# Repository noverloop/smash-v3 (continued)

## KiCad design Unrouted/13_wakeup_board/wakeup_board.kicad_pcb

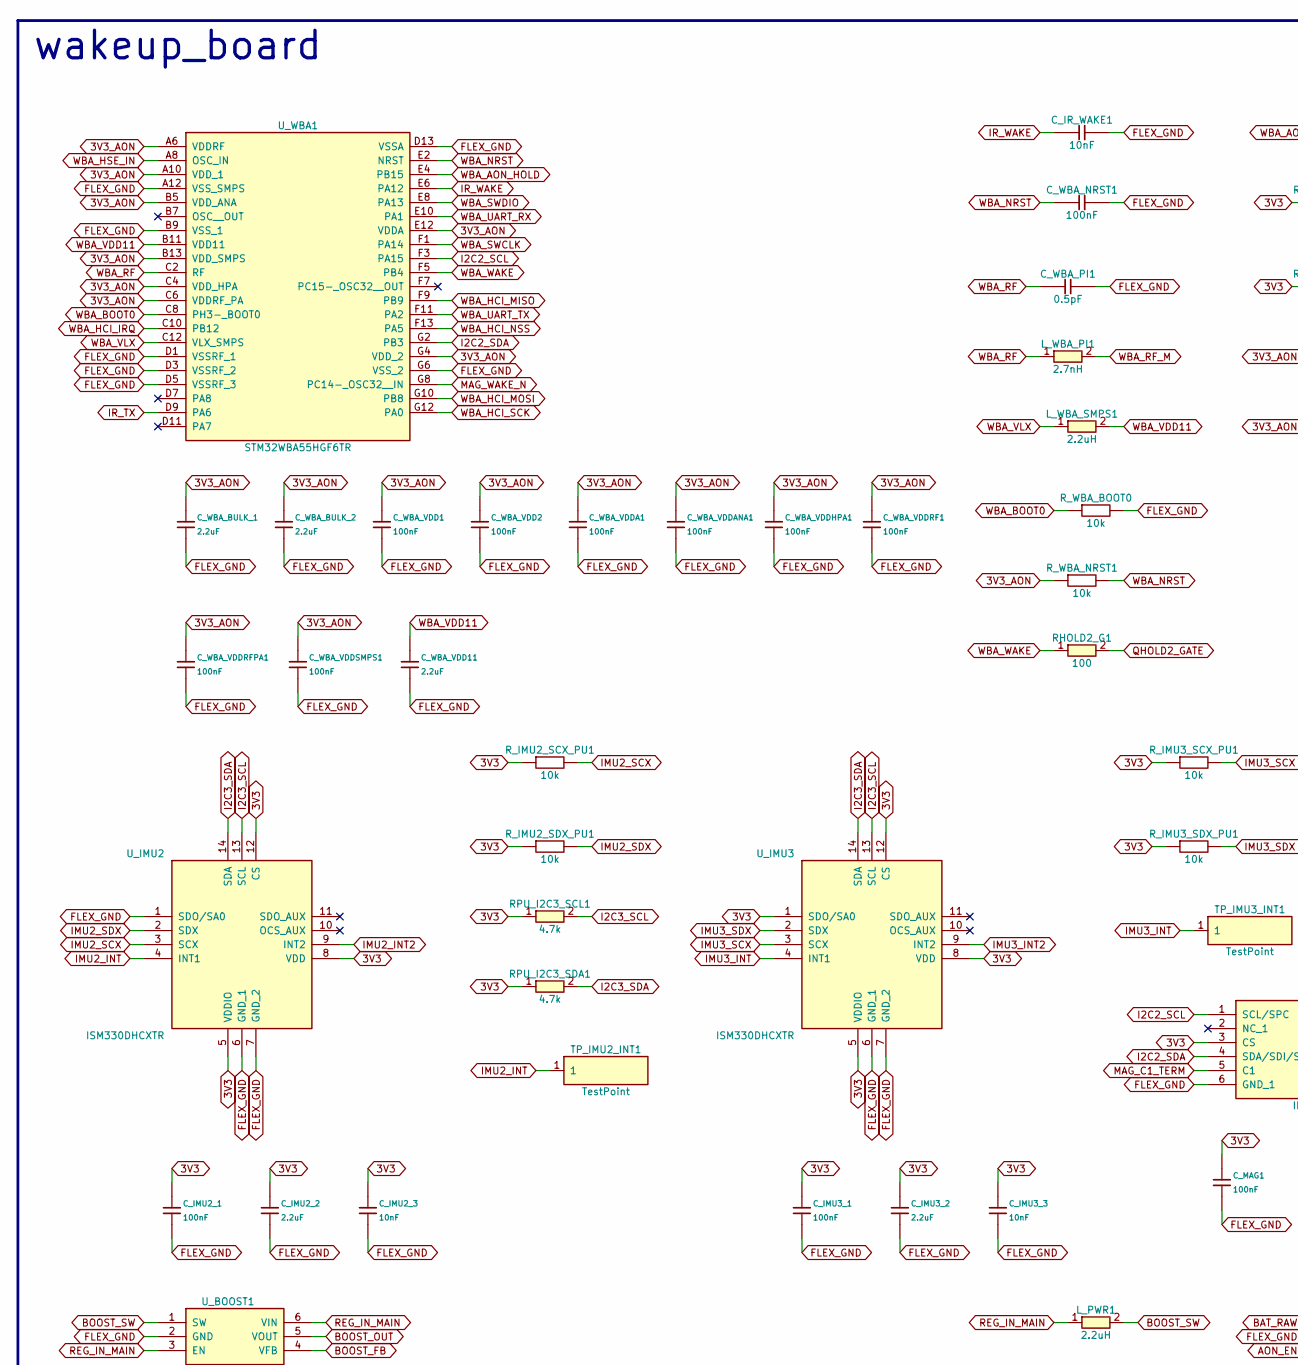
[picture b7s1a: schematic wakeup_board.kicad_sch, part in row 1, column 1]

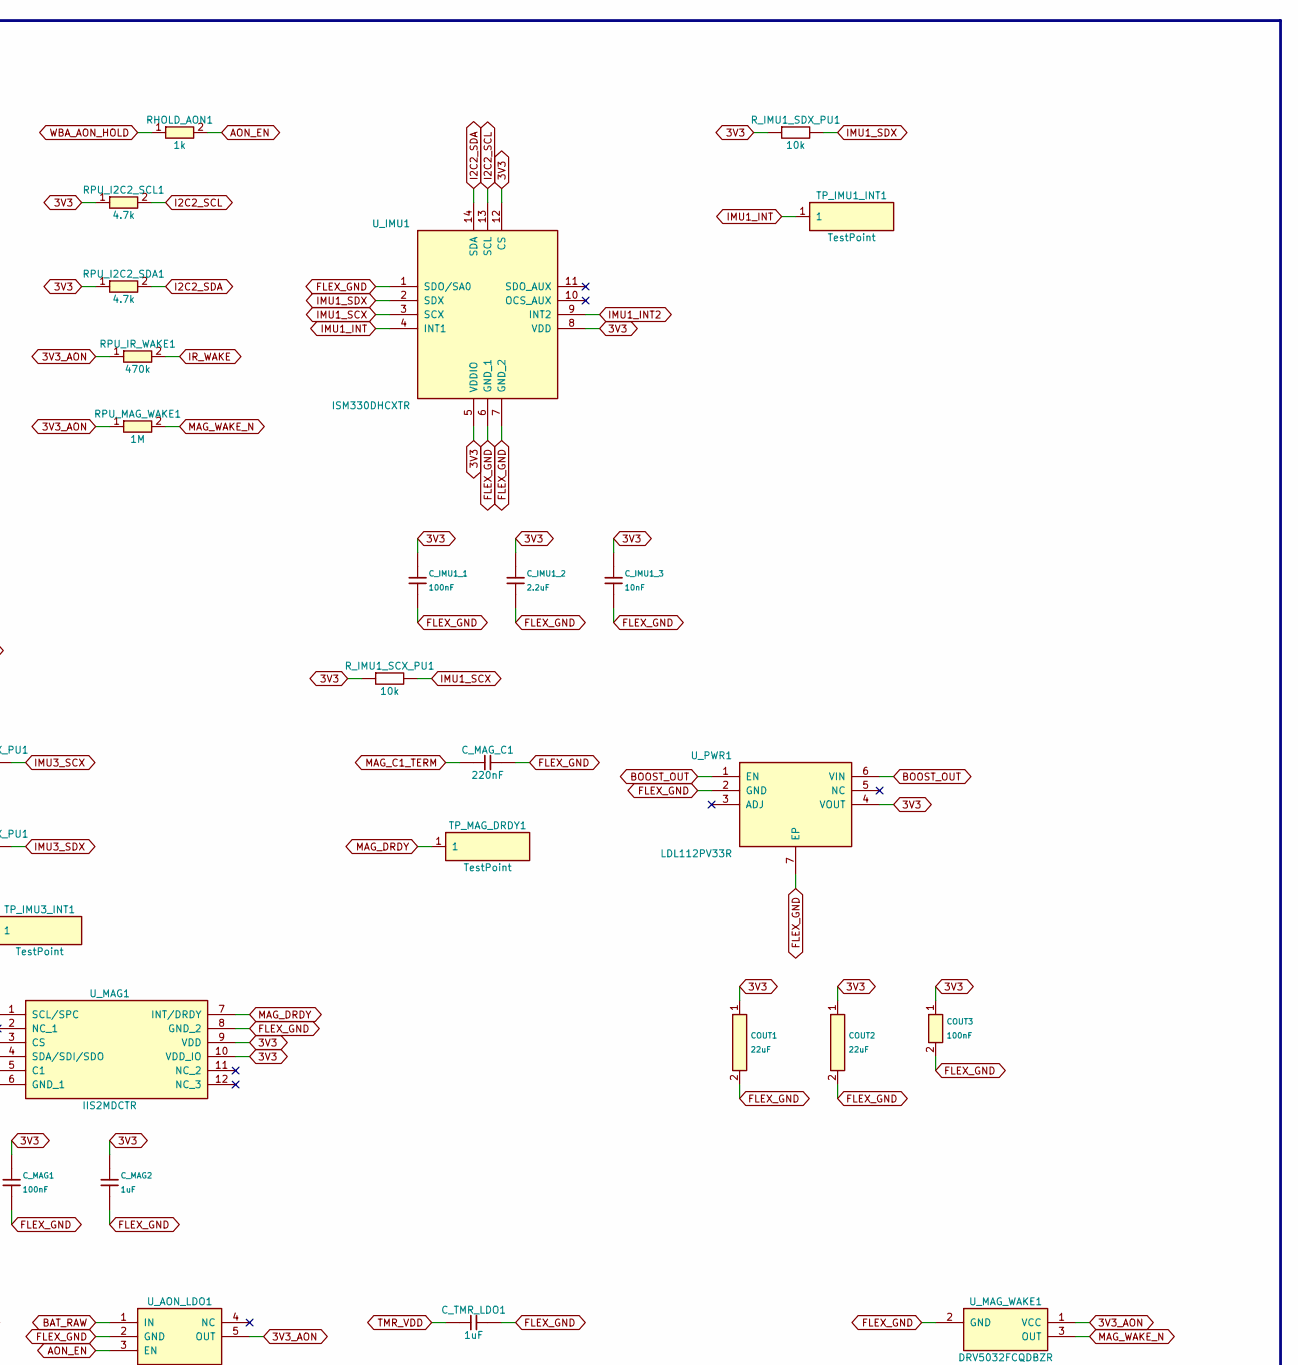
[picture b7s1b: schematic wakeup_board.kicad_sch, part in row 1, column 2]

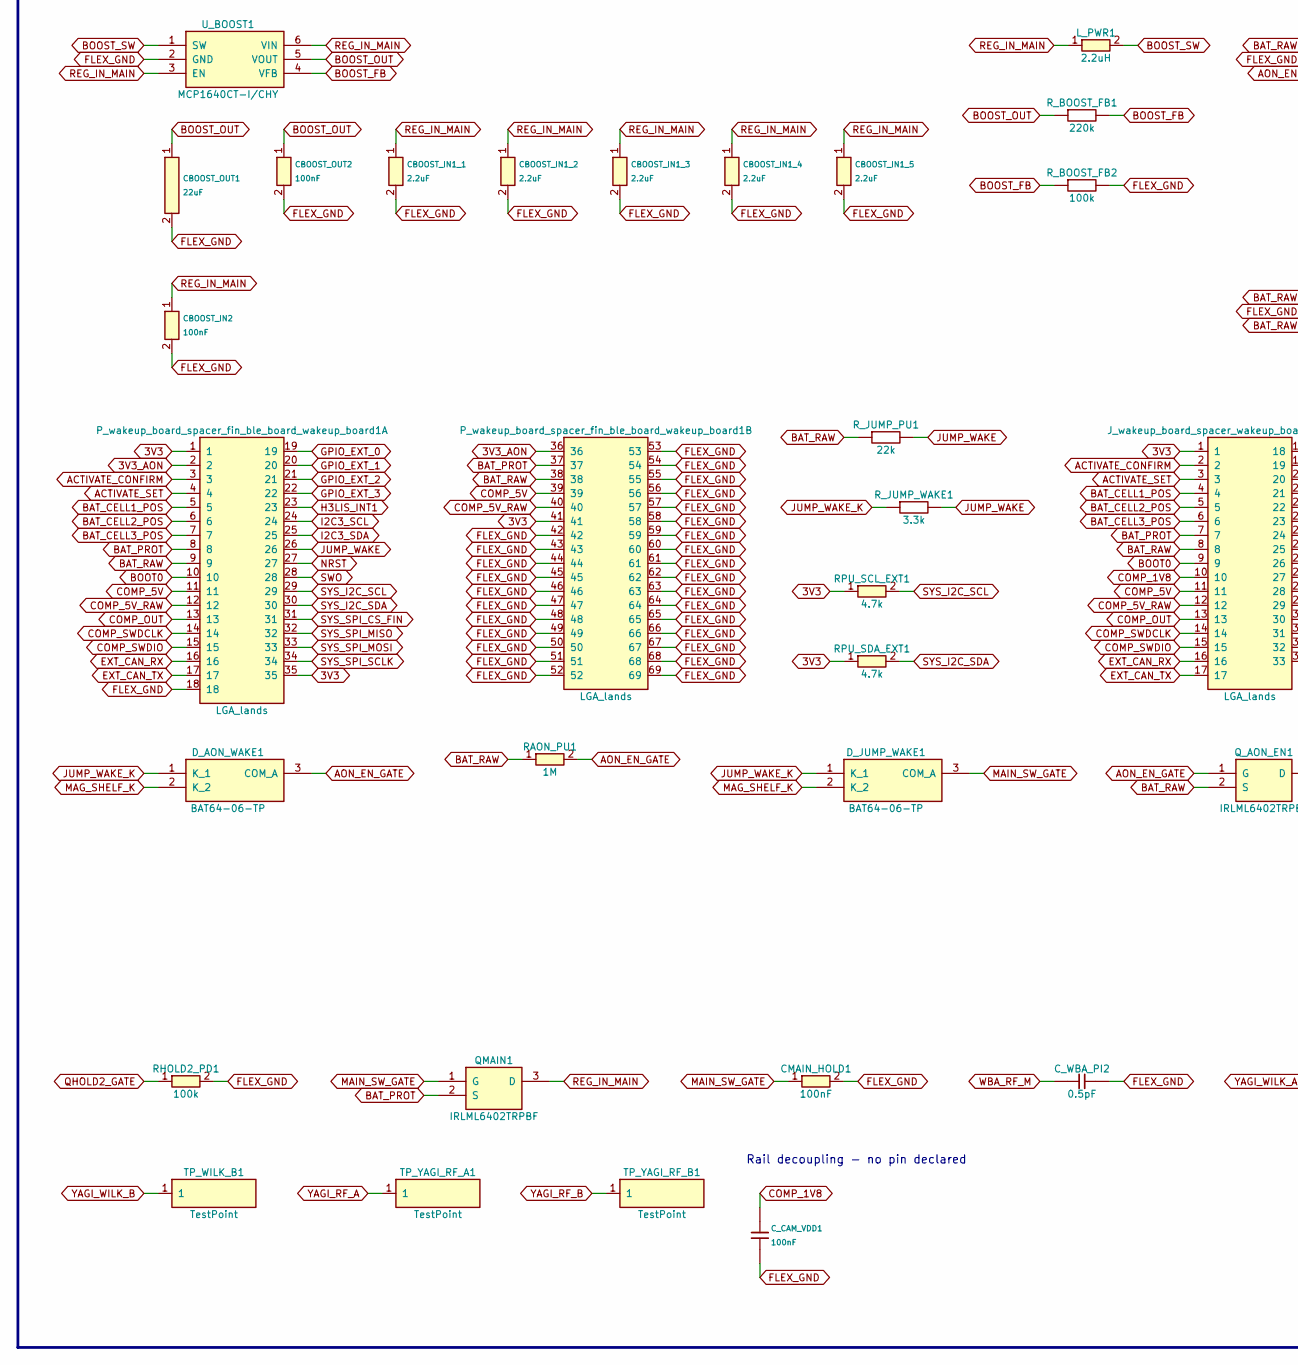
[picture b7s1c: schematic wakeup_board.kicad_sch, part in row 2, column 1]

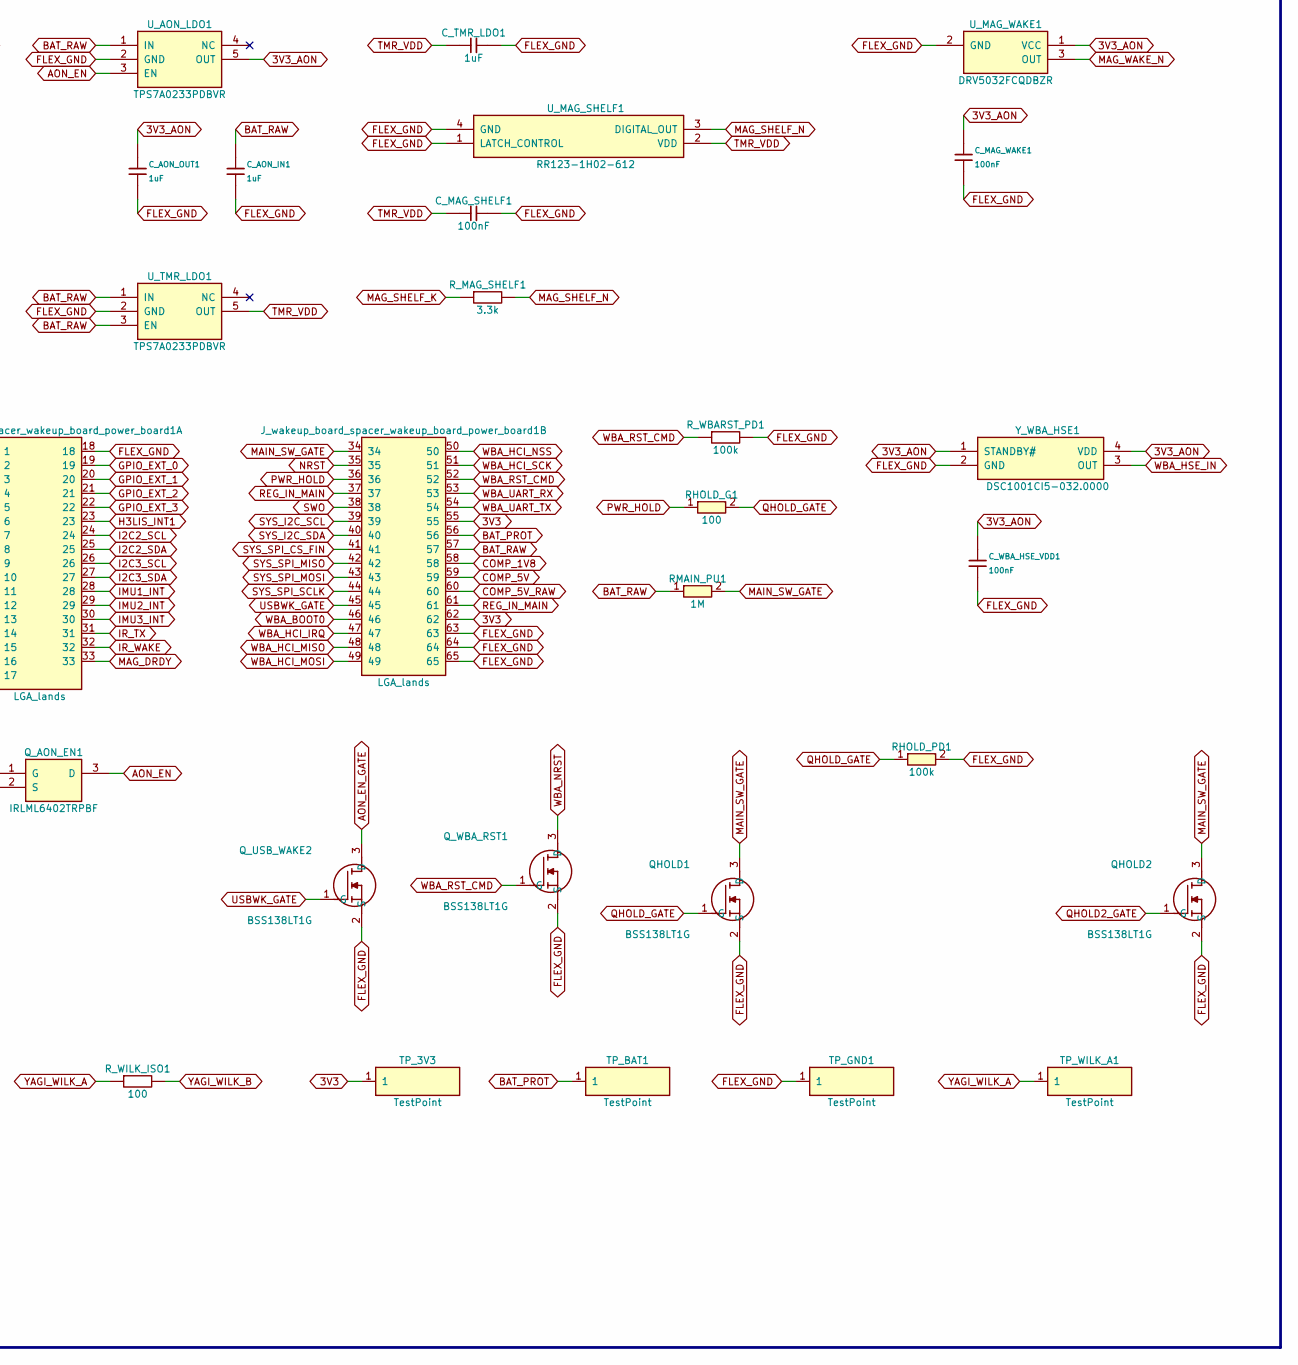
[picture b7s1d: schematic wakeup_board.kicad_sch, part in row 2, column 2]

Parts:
CBOOST_IN1_1, CBOOST_IN1_2, CBOOST_IN1_3, CBOOST_IN1_4, CBOOST_IN1_5: 2.2uF; Capacitor_SMD_C_0603_1608Metric; MPN C-Series MIL-PRF-32535 X7R 0603 2.2uF
CBOOST_IN2: 100nF; Capacitor_SMD_C_0402_1005Metric; MPN C0402 X7R 100nF
CBOOST_OUT1: 22uF; Capacitor_Tantalum_SMD_CP_EIA-3528-12_Kemet-T; MPN T491T 22uF (3528-12 thinnest variant)
CBOOST_OUT2: 100nF; Capacitor_SMD_C_0402_1005Metric; MPN C0402 X7R 100nF
CMAIN_HOLD1: 100nF; Capacitor_SMD_C_0402_1005Metric; MPN C0402 X7R 100nF
COUT1, COUT2: 22uF; Capacitor_Tantalum_SMD_CP_EIA-3528-12_Kemet-T; MPN T491T 22uF (3528-12 thinnest variant)
COUT3: 100nF; Capacitor_SMD_C_0402_1005Metric; MPN C0402 X7R 100nF
C_AON_IN1: 1uF; Capacitor_SMD_C_0805_2012Metric; MPN C-Series MIL-PRF-32535 X7R 0805 1uF
C_AON_OUT1: 1uF; Capacitor_SMD_C_0805_2012Metric; MPN C-Series MIL-PRF-32535 X7R 0805 1uF
C_CAM_VDD1: 100nF; Capacitor_SMD_C_0402_1005Metric; MPN C0402 X7R 100nF
C_IMU1_1, C_IMU2_1, C_IMU3_1: 100nF; Capacitor_SMD_C_0402_1005Metric; MPN C0402 X7R 100nF
C_IMU1_2, C_IMU2_2, C_IMU3_2: 2.2uF; Capacitor_SMD_C_0603_1608Metric; MPN C-Series MIL-PRF-32535 X7R 0603 2.2uF
C_IMU1_3, C_IMU2_3, C_IMU3_3: 10nF; Capacitor_SMD_C_0402_1005Metric; MPN C0402 X7R 10nF
C_IR_WAKE1: 10nF; Capacitor_SMD_C_0402_1005Metric; MPN C0402 X7R 10nF
C_MAG1: 100nF; Capacitor_SMD_C_0402_1005Metric; MPN C0402 X7R 100nF
C_MAG2: 1uF; Capacitor_SMD_C_0805_2012Metric; MPN C-Series MIL-PRF-32535 X7R 0805 1uF
C_MAG_C1: 220nF; Capacitor_SMD_C_0603_1608Metric; MPN C-Series MIL-PRF-32535 X7R 0603 220nF
C_MAG_SHELF1: 100nF; Capacitor_SMD_C_0402_1005Metric; MPN C0402 X7R 100nF
C_MAG_WAKE1: 100nF; Capacitor_SMD_C_0402_1005Metric; MPN C0402 X7R 100nF
C_TMR_LDO1: 1uF; Capacitor_SMD_C_0805_2012Metric; MPN C-Series MIL-PRF-32535 X7R 0805 1uF
C_WBA_BULK_1, C_WBA_BULK_2: 2.2uF; Capacitor_SMD_C_0603_1608Metric; MPN C-Series MIL-PRF-32535 X7R 0603 2.2uF
C_WBA_HSE_VDD1: 100nF; Capacitor_SMD_C_0402_1005Metric; MPN C0402 X7R 100nF
C_WBA_NRST1: 100nF; Capacitor_SMD_C_0402_1005Metric; MPN C0402 X7R 100nF
C_WBA_PI1: 0.5pF; Capacitor_SMD_C_0402_1005Metric; MPN TBD 0402 C0G/NP0 0.5pF (as placed; conf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
C_WBA_PI2: 0.5pF; Capacitor_SMD_C_0603_1608Metric; MPN SQCSVA 0.5pF
C_WBA_VDD1, C_WBA_VDD2: 100nF; Capacitor_SMD_C_0402_1005Metric; MPN C0402 X7R 100nF
C_WBA_VDD11: 2.2uF; Capacitor_SMD_C_0402_1005Metric; MPN TBD 0402 X5R 2.2uF (as placed; confirm 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
C_WBA_VDDA1: 100nF; Capacitor_SMD_C_0402_1005Metric; MPN C0402 X7R 100nF
C_WBA_VDDANA1: 100nF; Capacitor_SMD_C_0402_1005Metric; MPN C0402 X7R 100nF
C_WBA_VDDHPA1: 100nF; Capacitor_SMD_C_0402_1005Metric; MPN C0402 X7R 100nF
C_WBA_VDDRF1: 100nF; Capacitor_SMD_C_0402_1005Metric; MPN C0402 X7R 100nF
C_WBA_VDDRFPA1: 100nF; Capacitor_SMD_C_0402_1005Metric; MPN C0402 X7R 100nF
C_WBA_VDDSMPS1: 100nF; Capacitor_SMD_C_0402_1005Metric; MPN C0402 X7R 100nF
D_AON_WAKE1: BAT64-06-TP; SOT95P237X125-3N; MPN BAT64-06-TP
D_JUMP_WAKE1: BAT64-06-TP; SOT95P237X125-3N; MPN BAT64-06-TP
J_wakeup_board_spacer_wakeup_board_power_board1: LGA_lands; J_wakeup_board_spacer_wakeup_board_power_board; MPN LGA_lands
L_PWR1: 2.2uH; Inductor_SMD_L_2012_2.0x1.25mm; MPN TMS201210ALM-2R2MTAA
L_WBA_PI1: 2.7nH; Inductor_SMD_L_0402_1005Metric; MPN WE-KI 0402 2.7nH (74479xxxxx family)
L_WBA_SMPS1: 2.2uH; Inductor_SMD_L_2012_2.0x1.25mm; MPN TMS201210ALM-2R2MTAA
P_wakeup_board_spacer_fin_ble_board_wakeup_board1: LGA_lands; P_wakeup_board_spacer_fin_ble_board_wakeup_board; MPN LGA_lands
QHOLD1, QHOLD2: BSS138LT1G; SOT96P237X111-3N; MPN BSS138LT1G
QMAIN1: IRLML6402TRPBF; SOT95P237X112-3N; MPN IRLML6402TRPBF
Q_AON_EN1: IRLML6402TRPBF; SOT95P237X112-3N; MPN IRLML6402TRPBF
Q_USB_WAKE2: BSS138LT1G; SOT96P237X111-3N; MPN BSS138LT1G
Q_WBA_RST1: BSS138LT1G; SOT96P237X111-3N; MPN BSS138LT1G
RAON_PU1: 1M; Resistor_SMD_R_0402_1005Metric; MPN CRCW0402 1M 1% e3
RHOLD2_G1: 100; Resistor_SMD_R_0402_1005Metric; MPN CRCW0402 100 1% e3
RHOLD2_PD1: 100k; Resistor_SMD_R_0402_1005Metric; MPN CRCW0402 100k 1% e3
RHOLD_AON1: 1k; Resistor_SMD_R_0402_1005Metric; MPN CRCW0402 1k 1% e3
RHOLD_G1: 100; Resistor_SMD_R_0402_1005Metric; MPN CRCW0402 100 1% e3
RHOLD_PD1: 100k; Resistor_SMD_R_0402_1005Metric; MPN CRCW0402 100k 1% e3
RMAIN_PU1: 1M; Resistor_SMD_R_0402_1005Metric; MPN CRCW0402 1M 1% e3
RPU_I2C2_SCL1, RPU_I2C2_SDA1, RPU_I2C3_SCL1, RPU_I2C3_SDA1: 4.7k; Resistor_SMD_R_0402_1005Metric; MPN CRCW0402 4.7k 1% e3
RPU_IR_WAKE1: 470k; Resistor_SMD_R_0402_1005Metric; MPN CRCW0402 470k 1% e3
RPU_MAG_WAKE1: 1M; Resistor_SMD_R_0402_1005Metric; MPN CRCW0402 1M 1% e3
RPU_SCL_EXT1: 4.7k; Resistor_SMD_R_0402_1005Metric; MPN CRCW0402 4.7k 1% e3
RPU_SDA_EXT1: 4.7k; Resistor_SMD_R_0402_1005Metric; MPN CRCW0402 4.7k 1% e3
R_BOOST_FB1: 220k; Resistor_SMD_R_0402_1005Metric; MPN CRCW0402 220k 1% e3
R_BOOST_FB2: 100k; Resistor_SMD_R_0402_1005Metric; MPN CRCW0402 100k 1% e3
R_IMU1_SCX_PU1, R_IMU1_SDX_PU1, R_IMU2_SCX_PU1, R_IMU2_SDX_PU1, R_IMU3_SCX_PU1, R_IMU3_SDX_PU1: 10k; Resistor_SMD_R_0402_1005Metric; MPN CRCW0402 10k 1% e3
R_JUMP_PU1: 22k; Resistor_SMD_R_0402_1005Metric; MPN CRCW0402 22k 1% e3
R_JUMP_WAKE1: 3.3k; Resistor_SMD_R_0402_1005Metric; MPN CRCW0402 3.3k 1% e3
R_MAG_SHELF1: 3.3k; Resistor_SMD_R_0402_1005Metric; MPN CRCW0402 3.3k 1% e3
R_WBARST_PD1: 100k; Resistor_SMD_R_0402_1005Metric; MPN CRCW0402 100k 1% e3
R_WBA_BOOT0: 10k; Resistor_SMD_R_0402_1005Metric; MPN CRCW0402 10k 1% e3
R_WBA_NRST1: 10k; Resistor_SMD_R_0402_1005Metric; MPN CRCW0402 10k 1% e3
R_WILK_ISO1: 100; Resistor_SMD_R_0402_1005Metric; MPN CRCW0402 100 1% e3
TP_3V3: TestPoint; TestPoint_TestPoint_Pad_D1.5mm
TP_BAT1: TestPoint; TestPoint_TestPoint_Pad_D1.5mm
TP_GND1: TestPoint; TestPoint_TestPoint_Pad_D1.5mm
TP_IMU1_INT1, TP_IMU2_INT1, TP_IMU3_INT1: TestPoint; TestPoint_TestPoint_Pad_D1.5mm
TP_MAG_DRDY1: TestPoint; TestPoint_TestPoint_Pad_D1.5mm
TP_WILK_A1: TestPoint; TestPoint_TestPoint_Pad_D1.5mm
TP_WILK_B1: TestPoint; TestPoint_TestPoint_Pad_D1.5mm
TP_YAGI_RF_A1: TestPoint; TestPoint_TestPoint_Pad_D1.5mm
TP_YAGI_RF_B1: TestPoint; TestPoint_TestPoint_Pad_D1.5mm
U_AON_LDO1: TPS7A0233PDBVR; SOT95P280X145-5N; MPN TPS7A0233PDBVR
U_BOOST1: MCP1640CT-I/CHY; SOT95P270X145-6N; MPN MCP1640CT-I/CHY
U_IMU1, U_IMU2, U_IMU3: ISM330DHCXTR; LSM6DS3USTR (LGA-14); MPN ISM330DHCXTR
U_MAG1: IIS2MDCTR; MPN IIS2MDCTR
U_MAG_SHELF1: RR123-1H02-612; MPN RR123-1H02-612
U_MAG_WAKE1: DRV5032FCQDBZR; MPN DRV5032FCQDBZR
U_PWR1: LDL112PV33R; SON95P300X300X100-7N-D; MPN LDL112PV33R
U_TMR_LDO1: TPS7A0233PDBVR; SOT95P280X145-5N; MPN TPS7A0233PDBVR
U_WBA1: STM32WBA55HGF6TR; BGA41C35P13X7_298X276X50; MPN STM32WBA55HGF6TR
Y_WBA_HSE1: DSC1001CI5-032.0000; DSC1001CI50080000; MPN DSC1001CI5-032.0000

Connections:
3V3: COUT1.1 (+), COUT2.1 (+), COUT3.1, C_IMU1_1.1, C_IMU1_2.1, C_IMU1_3.1, C_IMU2_1.1, C_IMU2_2.1, C_IMU2_3.1, C_IMU3_1.1, C_IMU3_2.1, C_IMU3_3.1, C_MAG1.1, C_MAG2.1, J_wakeup_board_spacer_wakeup_board_powe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.1, J_wakeup_board_spacer_wakeup_board_powe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.55, J_wakeup_board_spacer_wakeup_board_powe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.62, P_wakeup_board_spacer_fin_ble_board_wak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.1, P_wakeup_board_spacer_fin_ble_board_wak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.35, P_wakeup_board_spacer_fin_ble_board_wak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.41, RPU_I2C2_SCL1.1, RPU_I2C2_SDA1.1, RPU_I2C3_SCL1.1, RPU_I2C3_SDA1.1, RPU_SCL_EXT1.1, RPU_SDA_EXT1.1, R_IMU1_SCX_PU1.1, R_IMU1_SDX_PU1.1, R_IMU2_SCX_PU1.1, R_IMU2_SDX_PU1.1, R_IMU3_SCX_PU1.1, R_IMU3_SDX_PU1.1, TP_3V3.1, U_IMU1.5 (VDDIO), U_IMU1.8 (VDD), U_IMU1.12 (CS), U_IMU2.5 (VDDIO), U_IMU2.8 (VDD), U_IMU2.12 (CS), U_IMU3.1 (SDO/SA0), U_IMU3.5 (VDDIO), U_IMU3.8 (VDD), U_IMU3.12 (CS), U_MAG1.3 (CS), U_MAG1.9 (VDD), U_MAG1.10 (VDD_IO), U_PWR1.4 (VOUT)
3V3_AON: C_AON_OUT1.1, C_MAG_WAKE1.1, C_WBA_BULK_1.1, C_WBA_BULK_2.1, C_WBA_HSE_VDD1.1, C_WBA_VDD1.1, C_WBA_VDD2.1, C_WBA_VDDA1.1, C_WBA_VDDANA1.1, C_WBA_VDDHPA1.1, C_WBA_VDDRF1.1, C_WBA_VDDRFPA1.1, C_WBA_VDDSMPS1.1, P_wakeup_board_spacer_fin_ble_board_wak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.2, P_wakeup_board_spacer_fin_ble_board_wak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.36, RPU_IR_WAKE1.1, RPU_MAG_WAKE1.1, R_WBA_NRST1.1, U_AON_LDO1.5 (OUT), U_MAG_WAKE1.1 (VCC), U_WBA1.A6 (VDDRF), U_WBA1.A10 (VDD_1), U_WBA1.B5 (VDD_ANA), U_WBA1.B13 (VDD_SMPS), U_WBA1.C4 (VDD_HPA), U_WBA1.C6 (VDDRF_PA), U_WBA1.E12 (VDDA), U_WBA1.G4 (VDD_2), Y_WBA_HSE1.1 (STANDBY#), Y_WBA_HSE1.4 (VDD)
ACTIVATE_CONFIRM: J_wakeup_board_spacer_wakeup_board_powe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.2, P_wakeup_board_spacer_fin_ble_board_wak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.3
ACTIVATE_SET: J_wakeup_board_spacer_wakeup_board_powe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.3, P_wakeup_board_spacer_fin_ble_board_wak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.4
AON_EN: Q_AON_EN1.3 (D), RHOLD_AON1.2, U_AON_LDO1.3 (EN)
AON_EN_GATE: D_AON_WAKE1.3 (COM_A), Q_AON_EN1.1 (G), Q_USB_WAKE2.3 (D), RAON_PU1.2
BAT_CELL1_POS: J_wakeup_board_spacer_wakeup_board_powe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.4, P_wakeup_board_spacer_fin_ble_board_wak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.5
BAT_CELL2_POS: J_wakeup_board_spacer_wakeup_board_powe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.5, P_wakeup_board_spacer_fin_ble_board_wak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.6
BAT_CELL3_POS: J_wakeup_board_spacer_wakeup_board_powe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.6, P_wakeup_board_spacer_fin_ble_board_wak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.7
BAT_PROT: J_wakeup_board_spacer_wakeup_board_powe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.7, J_wakeup_board_spacer_wakeup_board_powe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.56, P_wakeup_board_spacer_fin_ble_board_wak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.8, P_wakeup_board_spacer_fin_ble_board_wak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.37, QMAIN1.2 (S), TP_BAT1.1
BAT_RAW: C_AON_IN1.1, J_wakeup_board_spacer_wakeup_board_powe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.8, J_wakeup_board_spacer_wakeup_board_powe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.57, P_wakeup_board_spacer_fin_ble_board_wak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.9, P_wakeup_board_spacer_fin_ble_board_wak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.38, Q_AON_EN1.2 (S), RAON_PU1.1, RMAIN_PU1.1, R_JUMP_PU1.1, U_AON_LDO1.1 (IN), U_TMR_LDO1.1 (IN), U_TMR_LDO1.3 (EN)
BOOST_FB: R_BOOST_FB1.2, R_BOOST_FB2.1, U_BOOST1.4 (VFB)
BOOST_OUT: CBOOST_OUT1.1 (+), CBOOST_OUT2.1, R_BOOST_FB1.1, U_BOOST1.5 (VOUT), U_PWR1.1 (EN), U_PWR1.6 (VIN)
BOOST_SW: L_PWR1.2, U_BOOST1.1 (SW)
BOOT0: J_wakeup_board_spacer_wakeup_board_powe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.9, P_wakeup_board_spacer_fin_ble_board_wak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.10
COMP_1V8: C_CAM_VDD1.1, J_wakeup_board_spacer_wakeup_board_powe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.10, J_wakeup_board_spacer_wakeup_board_powe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.58
COMP_5V: J_wakeup_board_spacer_wakeup_board_powe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.11, J_wakeup_board_spacer_wakeup_board_powe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.59, P_wakeup_board_spacer_fin_ble_board_wak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.11, P_wakeup_board_spacer_fin_ble_board_wak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.39
COMP_5V_RAW: J_wakeup_board_spacer_wakeup_board_powe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.12, J_wakeup_board_spacer_wakeup_board_powe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.60, P_wakeup_board_spacer_fin_ble_board_wak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.12, P_wakeup_board_spacer_fin_ble_board_wak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.40
COMP_OUT: J_wakeup_board_spacer_wakeup_board_powe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.13, P_wakeup_board_spacer_fin_ble_board_wak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.13
COMP_SWDCLK: J_wakeup_board_spacer_wakeup_board_powe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.14, P_wakeup_board_spacer_fin_ble_board_wak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.14
COMP_SWDIO: J_wakeup_board_spacer_wakeup_board_powe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.15, P_wakeup_board_spacer_fin_ble_board_wak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.15
EXT_CAN_RX: J_wakeup_board_spacer_wakeup_board_powe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.16, P_wakeup_board_spacer_fin_ble_board_wak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.16
EXT_CAN_TX: J_wakeup_board_spacer_wakeup_board_powe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.17, P_wakeup_board_spacer_fin_ble_board_wak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.17
FLEX_GND: CBOOST_IN1_1.2, CBOOST_IN1_2.2, CBOOST_IN1_3.2, CBOOST_IN1_4.2, CBOOST_IN1_5.2, CBOOST_IN2.2, CBOOST_OUT1.2 (-), CBOOST_OUT2.2, CMAIN_HOLD1.2, COUT1.2 (-), COUT2.2 (-), COUT3.2, C_AON_IN1.2, C_AON_OUT1.2, C_CAM_VDD1.2, C_IMU1_1.2, C_IMU1_2.2, C_IMU1_3.2, C_IMU2_1.2, C_IMU2_2.2, C_IMU2_3.2, C_IMU3_1.2, C_IMU3_2.2, C_IMU3_3.2, C_IR_WAKE1.2, C_MAG1.2, C_MAG2.2, C_MAG_C1.2, C_MAG_SHELF1.2, C_MAG_WAKE1.2, C_TMR_LDO1.2, C_WBA_BULK_1.2, C_WBA_BULK_2.2, C_WBA_HSE_VDD1.2, C_WBA_NRST1.2, C_WBA_PI1.2, C_WBA_PI2.2, C_WBA_VDD1.2, C_WBA_VDD2.2, C_WBA_VDD11.2, C_WBA_VDDA1.2, C_WBA_VDDANA1.2, C_WBA_VDDHPA1.2, C_WBA_VDDRF1.2, C_WBA_VDDRFPA1.2, C_WBA_VDDSMPS1.2, J_wakeup_board_spacer_wakeup_board_powe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.18, J_wakeup_board_spacer_wakeup_board_powe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.63, J_wakeup_board_spacer_wakeup_board_powe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.64, J_wakeup_board_spacer_wakeup_board_powe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.65, P_wakeup_board_spacer_fin_ble_board_wak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.18, P_wakeup_board_spacer_fin_ble_board_wak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.42, P_wakeup_board_spacer_fin_ble_board_wak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.43, P_wakeup_board_spacer_fin_ble_board_wak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.44, P_wakeup_board_spacer_fin_ble_board_wak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.45, P_wakeup_board_spacer_fin_ble_board_wak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.46, P_wakeup_board_spacer_fin_ble_board_wak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.47, P_wakeup_board_spacer_fin_ble_board_wak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.48, P_wakeup_board_spacer_fin_ble_board_wak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.49, P_wakeup_board_spacer_fin_ble_board_wak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.50, P_wakeup_board_spacer_fin_ble_board_wak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.51, P_wakeup_board_spacer_fin_ble_board_wak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.52, P_wakeup_board_spacer_fin_ble_board_wak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.53, P_wakeup_board_spacer_fin_ble_board_wak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.54, P_wakeup_board_spacer_fin_ble_board_wak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.55, P_wakeup_board_spacer_fin_ble_board_wak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.56, P_wakeup_board_spacer_fin_ble_board_wak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.57, P_wakeup_board_spacer_fin_ble_board_wak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.58, P_wakeup_board_spacer_fin_ble_board_wak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.59, P_wakeup_board_spacer_fin_ble_board_wak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.60, P_wakeup_board_spacer_fin_ble_board_wak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.61, P_wakeup_board_spacer_fin_ble_board_wak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.62, P_wakeup_board_spacer_fin_ble_board_wak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.63, P_wakeup_board_spacer_fin_ble_board_wak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.64, P_wakeup_board_spacer_fin_ble_board_wak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.65, P_wakeup_board_spacer_fin_ble_board_wak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.66, P_wakeup_board_spacer_fin_ble_board_wak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.67, P_wakeup_board_spacer_fin_ble_board_wak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.68, P_wakeup_board_spacer_fin_ble_board_wak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.69, QHOLD1.2 (S), QHOLD2.2 (S), Q_USB_WAKE2.2 (S), Q_WBA_RST1.2 (S), RHOLD2_PD1.2, RHOLD_PD1.2, R_BOOST_FB2.2, R_WBARST_PD1.2, R_WBA_BOOT0.2, TP_GND1.1, U_AON_LDO1.2 (GND), U_BOOST1.2 (GND), U_IMU1.1 (SDO/SA0), U_IMU1.6 (GND_1), U_IMU1.7 (GND_2), U_IMU2.1 (SDO/SA0), U_IMU2.6 (GND_1), U_IMU2.7 (GND_2), U_IMU3.6 (GND_1), U_IMU3.7 (GND_2), U_MAG1.6 (GND_1), U_MAG1.8 (GND_2), U_MAG_SHELF1.1 (LATCH_CONTROL), U_MAG_SHELF1.4 (GND), U_MAG_WAKE1.2 (GND), U_PWR1.2 (GND), U_PWR1.7 (EP), U_TMR_LDO1.2 (GND), U_WBA1.A12 (VSS_SMPS), U_WBA1.B9 (VSS_1), U_WBA1.D1 (VSSRF_1), U_WBA1.D3 (VSSRF_2), U_WBA1.D5 (VSSRF_3), U_WBA1.D13 (VSSA), U_WBA1.G6 (VSS_2), Y_WBA_HSE1.2 (GND)
GPIO_EXT_0: J_wakeup_board_spacer_wakeup_board_powe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.19, P_wakeup_board_spacer_fin_ble_board_wak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.19
GPIO_EXT_1: J_wakeup_board_spacer_wakeup_board_powe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.20, P_wakeup_board_spacer_fin_ble_board_wak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.20
GPIO_EXT_2: J_wakeup_board_spacer_wakeup_board_powe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.21, P_wakeup_board_spacer_fin_ble_board_wak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.21
GPIO_EXT_3: J_wakeup_board_spacer_wakeup_board_powe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.22, P_wakeup_board_spacer_fin_ble_board_wak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.22
H3LIS_INT1: J_wakeup_board_spacer_wakeup_board_powe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.23, P_wakeup_board_spacer_fin_ble_board_wak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.23
I2C2_SCL: J_wakeup_board_spacer_wakeup_board_powe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.24, RPU_I2C2_SCL1.2, U_IMU1.13 (SCL), U_MAG1.1 (SCL/SPC), U_WBA1.F3 (PA15)
I2C2_SDA: J_wakeup_board_spacer_wakeup_board_powe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.25, RPU_I2C2_SDA1.2, U_IMU1.14 (SDA), U_MAG1.4 (SDA/SDI/SDO), U_WBA1.G2 (PB3)
I2C3_SCL: J_wakeup_board_spacer_wakeup_board_powe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.26, P_wakeup_board_spacer_fin_ble_board_wak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.24, RPU_I2C3_SCL1.2, U_IMU2.13 (SCL), U_IMU3.13 (SCL)
I2C3_SDA: J_wakeup_board_spacer_wakeup_board_powe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.27, P_wakeup_board_spacer_fin_ble_board_wak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.25, RPU_I2C3_SDA1.2, U_IMU2.14 (SDA), U_IMU3.14 (SDA)
IMU1_INT: J_wakeup_board_spacer_wakeup_board_powe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.28, TP_IMU1_INT1.1, U_IMU1.4 (INT1)
IMU1_INT2: U_IMU1.9 (INT2)
IMU1_SCX: R_IMU1_SCX_PU1.2, U_IMU1.3 (SCX)
IMU1_SDX: R_IMU1_SDX_PU1.2, U_IMU1.2 (SDX)
IMU2_INT: J_wakeup_board_spacer_wakeup_board_powe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.29, TP_IMU2_INT1.1, U_IMU2.4 (INT1)
IMU2_INT2: U_IMU2.9 (INT2)
IMU2_SCX: R_IMU2_SCX_PU1.2, U_IMU2.3 (SCX)
IMU2_SDX: R_IMU2_SDX_PU1.2, U_IMU2.2 (SDX)
IMU3_INT: J_wakeup_board_spacer_wakeup_board_powe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.30, TP_IMU3_INT1.1, U_IMU3.4 (INT1)
IMU3_INT2: U_IMU3.9 (INT2)
IMU3_SCX: R_IMU3_SCX_PU1.2, U_IMU3.3 (SCX)
IMU3_SDX: R_IMU3_SDX_PU1.2, U_IMU3.2 (SDX)
IR_TX: J_wakeup_board_spacer_wakeup_board_powe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.31, U_WBA1.D9 (PA6)
IR_WAKE: C_IR_WAKE1.1, J_wakeup_board_spacer_wakeup_board_powe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.32, RPU_IR_WAKE1.2, U_WBA1.E6 (PA12)
JUMP_WAKE: P_wakeup_board_spacer_fin_ble_board_wak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.26, R_JUMP_PU1.2, R_JUMP_WAKE1.2
JUMP_WAKE_K: D_AON_WAKE1.1 (K_1), D_JUMP_WAKE1.1 (K_1), R_JUMP_WAKE1.1
MAG_C1_TERM: C_MAG_C1.1, U_MAG1.5 (C1)
MAG_DRDY: J_wakeup_board_spacer_wakeup_board_powe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.33, TP_MAG_DRDY1.1, U_MAG1.7 (INT/DRDY)
MAG_SHELF_K: D_AON_WAKE1.2 (K_2), D_JUMP_WAKE1.2 (K_2), R_MAG_SHELF1.1
MAG_SHELF_N: R_MAG_SHELF1.2, U_MAG_SHELF1.3 (DIGITAL_OUT)
MAG_WAKE_N: RPU_MAG_WAKE1.2, U_MAG_WAKE1.3 (OUT), U_WBA1.G8 (PC14-_OSC32__IN)
MAIN_SW_GATE: CMAIN_HOLD1.1, D_JUMP_WAKE1.3 (COM_A), J_wakeup_board_spacer_wakeup_board_powe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.34, QHOLD1.3 (D), QHOLD2.3 (D), QMAIN1.1 (G), RMAIN_PU1.2
NRST: J_wakeup_board_spacer_wakeup_board_powe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.35, P_wakeup_board_spacer_fin_ble_board_wak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.27
PWR_HOLD: J_wakeup_board_spacer_wakeup_board_powe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.36, RHOLD_G1.1
QHOLD2_GATE: QHOLD2.1 (G), RHOLD2_G1.2, RHOLD2_PD1.1
QHOLD_GATE: QHOLD1.1 (G), RHOLD_G1.2, RHOLD_PD1.1
REG_IN_MAIN: CBOOST_IN1_1.1, CBOOST_IN1_2.1, CBOOST_IN1_3.1, CBOOST_IN1_4.1, CBOOST_IN1_5.1, CBOOST_IN2.1, J_wakeup_board_spacer_wakeup_board_powe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.37, J_wakeup_board_spacer_wakeup_board_powe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.61, L_PWR1.1, QMAIN1.3 (D), U_BOOST1.3 (EN), U_BOOST1.6 (VIN)
SWO: J_wakeup_board_spacer_wakeup_board_powe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.38, P_wakeup_board_spacer_fin_ble_board_wak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.28
SYS_I2C_SCL: J_wakeup_board_spacer_wakeup_board_powe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.39, P_wakeup_board_spacer_fin_ble_board_wak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.29, RPU_SCL_EXT1.2
SYS_I2C_SDA: J_wakeup_board_spacer_wakeup_board_powe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.40, P_wakeup_board_spacer_fin_ble_board_wak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.30, RPU_SDA_EXT1.2
SYS_SPI_CS_FIN: J_wakeup_board_spacer_wakeup_board_powe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.41, P_wakeup_board_spacer_fin_ble_board_wak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.31
SYS_SPI_MISO: J_wakeup_board_spacer_wakeup_board_powe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.42, P_wakeup_board_spacer_fin_ble_board_wak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.32
SYS_SPI_MOSI: J_wakeup_board_spacer_wakeup_board_powe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.43, P_wakeup_board_spacer_fin_ble_board_wak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.33
SYS_SPI_SCLK: J_wakeup_board_spacer_wakeup_board_powe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.44, P_wakeup_board_spacer_fin_ble_board_wak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.34
TMR_VDD: C_MAG_SHELF1.1, C_TMR_LDO1.1, U_MAG_SHELF1.2 (VDD), U_TMR_LDO1.5 (OUT)
USBWK_GATE: J_wakeup_board_spacer_wakeup_board_powe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.45, Q_USB_WAKE2.1 (G)
WBA_AON_HOLD: RHOLD_AON1.1, U_WBA1.E4 (PB15)
WBA_BOOT0: J_wakeup_board_spacer_wakeup_board_powe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.46, R_WBA_BOOT0.1, U_WBA1.C8 (PH3-_BOOT0)
WBA_HCI_IRQ: J_wakeup_board_spacer_wakeup_board_powe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.47, U_WBA1.C10 (PB12)
WBA_HCI_MISO: J_wakeup_board_spacer_wakeup_board_powe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.48, U_WBA1.F9 (PB9)
WBA_HCI_MOSI: J_wakeup_board_spacer_wakeup_board_powe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.49, U_WBA1.G10 (PB8)
WBA_HCI_NSS: J_wakeup_board_spacer_wakeup_board_powe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.50, U_WBA1.F13 (PA5)
WBA_HCI_SCK: J_wakeup_board_spacer_wakeup_board_powe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.51, U_WBA1.G12 (PA0)
WBA_HSE_IN: U_WBA1.A8 (OSC_IN), Y_WBA_HSE1.3 (OUT)
WBA_NRST: C_WBA_NRST1.1, Q_WBA_RST1.3 (D), R_WBA_NRST1.2, U_WBA1.E2 (NRST)
WBA_RF: C_WBA_PI1.1, L_WBA_PI1.1, U_WBA1.C2 (RF)
WBA_RF_M: C_WBA_PI2.1, L_WBA_PI1.2
WBA_RST_CMD: J_wakeup_board_spacer_wakeup_board_powe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.52, Q_WBA_RST1.1 (G), R_WBARST_PD1.1
WBA_SWCLK: U_WBA1.F1 (PA14)
WBA_SWDIO: U_WBA1.E8 (PA13)
WBA_UART_RX: J_wakeup_board_spacer_wakeup_board_powe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.53, U_WBA1.E10 (PA1)
WBA_UART_TX: J_wakeup_board_spacer_wakeup_board_powe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.54, U_WBA1.F11 (PA2)
WBA_VDD11: C_WBA_VDD11.1, L_WBA_SMPS1.2, U_WBA1.B11 (VDD11)
WBA_VLX: L_WBA_SMPS1.1, U_WBA1.C12 (VLX_SMPS)
WBA_WAKE: RHOLD2_G1.1, U_WBA1.F5 (PB4)
YAGI_RF_A: TP_YAGI_RF_A1.1
YAGI_RF_B: TP_YAGI_RF_B1.1
YAGI_WILK_A: R_WILK_ISO1.1, TP_WILK_A1.1
YAGI_WILK_B: R_WILK_ISO1.2, TP_WILK_B1.1

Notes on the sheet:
wakeup_board
Rail decoupling - no pin declared

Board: 14 copper layers, 114 parts (80 on the bottom side), 85 nets, no tracks yet.

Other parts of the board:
MH1, MH2: smash_mech_potting
